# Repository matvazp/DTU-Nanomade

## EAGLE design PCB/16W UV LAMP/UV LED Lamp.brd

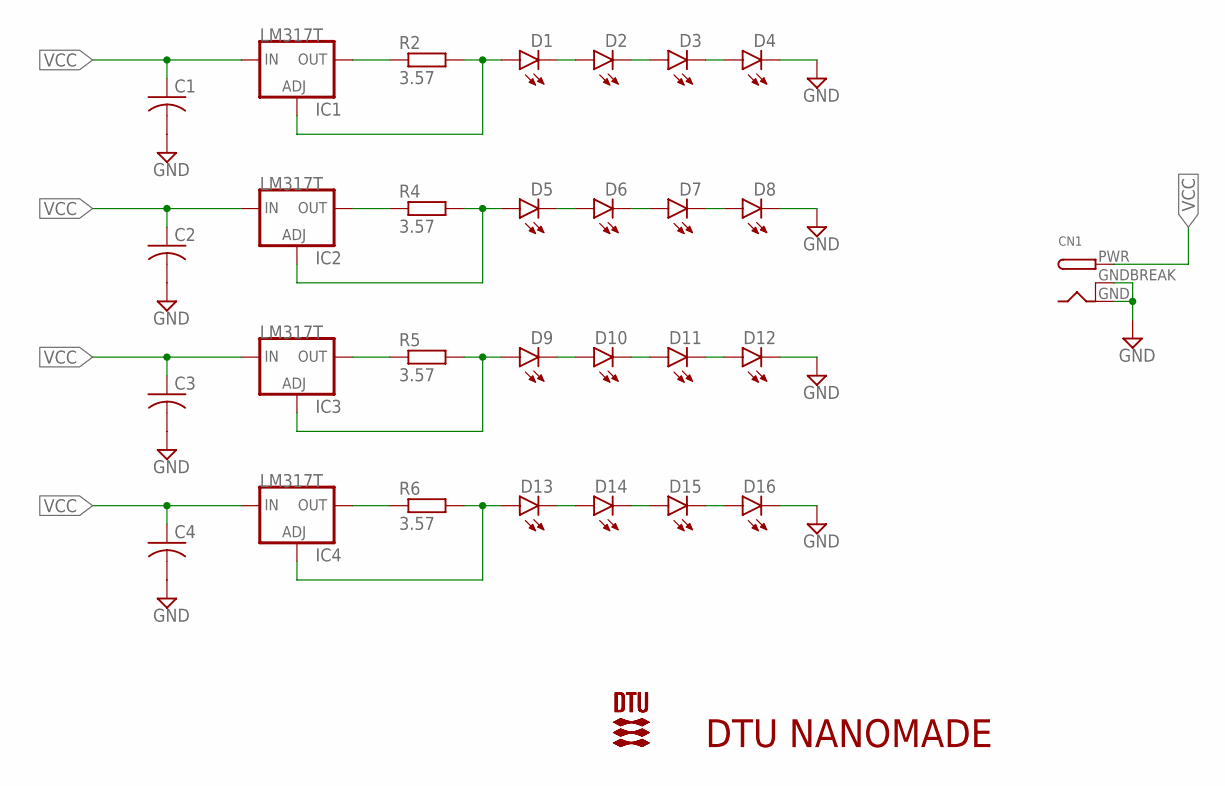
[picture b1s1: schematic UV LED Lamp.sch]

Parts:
C1, C2, C3, C4: C-USC0805K; C0805K
CN1: DCBARRELPTH; DCJACK_2MM_PTH
D1, D2, D3, D4, D5, D6, D7, D8, D9, D10, D11, D12, D13, D14, D15, D16: PM2L-1LLE-LC
IC1, IC2, IC3, IC4: LM317T; 317TL
R2, R4, R5, R6: 3.57; 0207/7
U$1, U$2: DTU_LOGO

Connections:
GND: C1.2, C2.2, C3.2, C4.2, CN1.GND, CN1.GNDBREAK, D4.P$1 (C), D8.P$1 (C), D12.P$1 (C), D16.P$1 (C)
unnamed: D1.P$1 (C), D2.P$2 (A)
unnamed: D2.P$1 (C), D3.P$2 (A)
unnamed: D3.P$1 (C), D4.P$2 (A)
unnamed: IC1.2 (OUT), R2.1
unnamed: D6.P$1 (C), D7.P$2 (A)
unnamed: D7.P$1 (C), D8.P$2 (A)
unnamed: IC2.2 (OUT), R4.1
unnamed: D9.P$1 (C), D10.P$2 (A)
unnamed: D14.P$1 (C), D15.P$2 (A)
unnamed: D13.P$1 (C), D14.P$2 (A)
unnamed: IC3.2 (OUT), R5.1
unnamed: D11.P$1 (C), D12.P$2 (A)
unnamed: D5.P$1 (C), D6.P$2 (A)
unnamed: D10.P$1 (C), D11.P$2 (A)
unnamed: D15.P$1 (C), D16.P$2 (A)
unnamed: IC4.2 (OUT), R6.1
unnamed: D1.P$2 (A), IC1.1 (ADJ), R2.2
unnamed: D5.P$2 (A), IC2.1 (ADJ), R4.2
unnamed: D9.P$2 (A), IC3.1 (ADJ), R5.2
unnamed: D13.P$2 (A), IC4.1 (ADJ), R6.2
VCC: C1.1, C2.1, C3.1, C4.1, CN1.PWR, IC1.3 (IN), IC2.3 (IN), IC3.3 (IN), IC4.3 (IN)

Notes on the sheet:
DTU NANOMADE

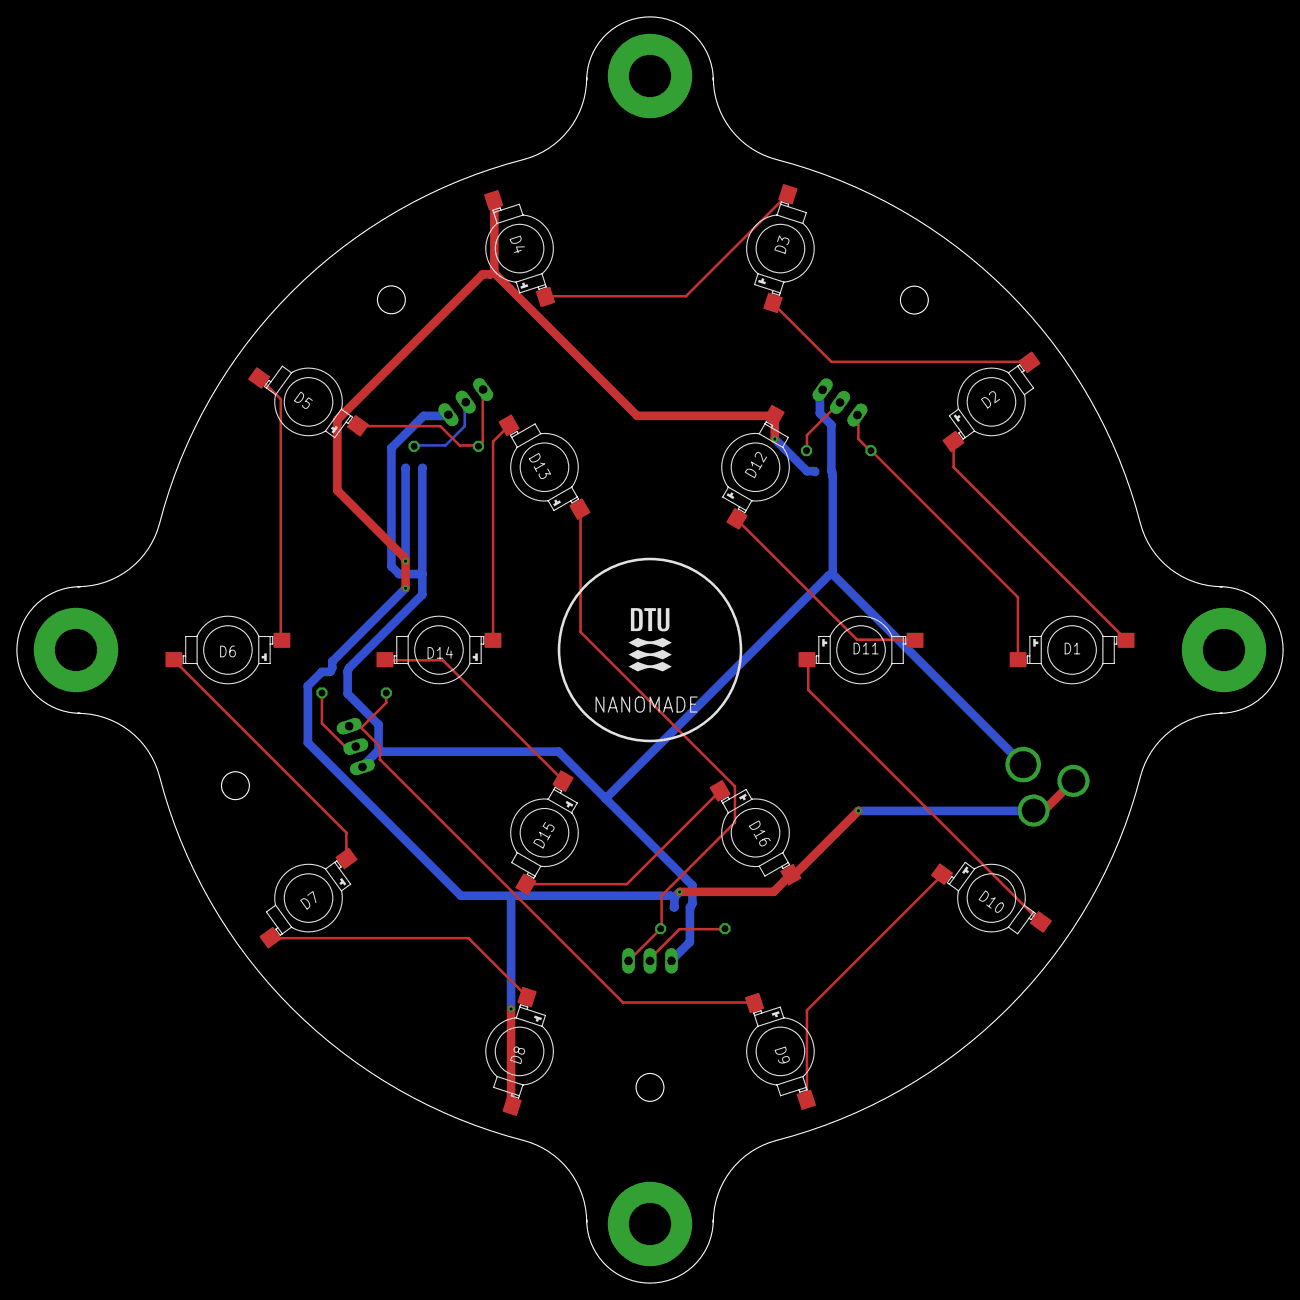
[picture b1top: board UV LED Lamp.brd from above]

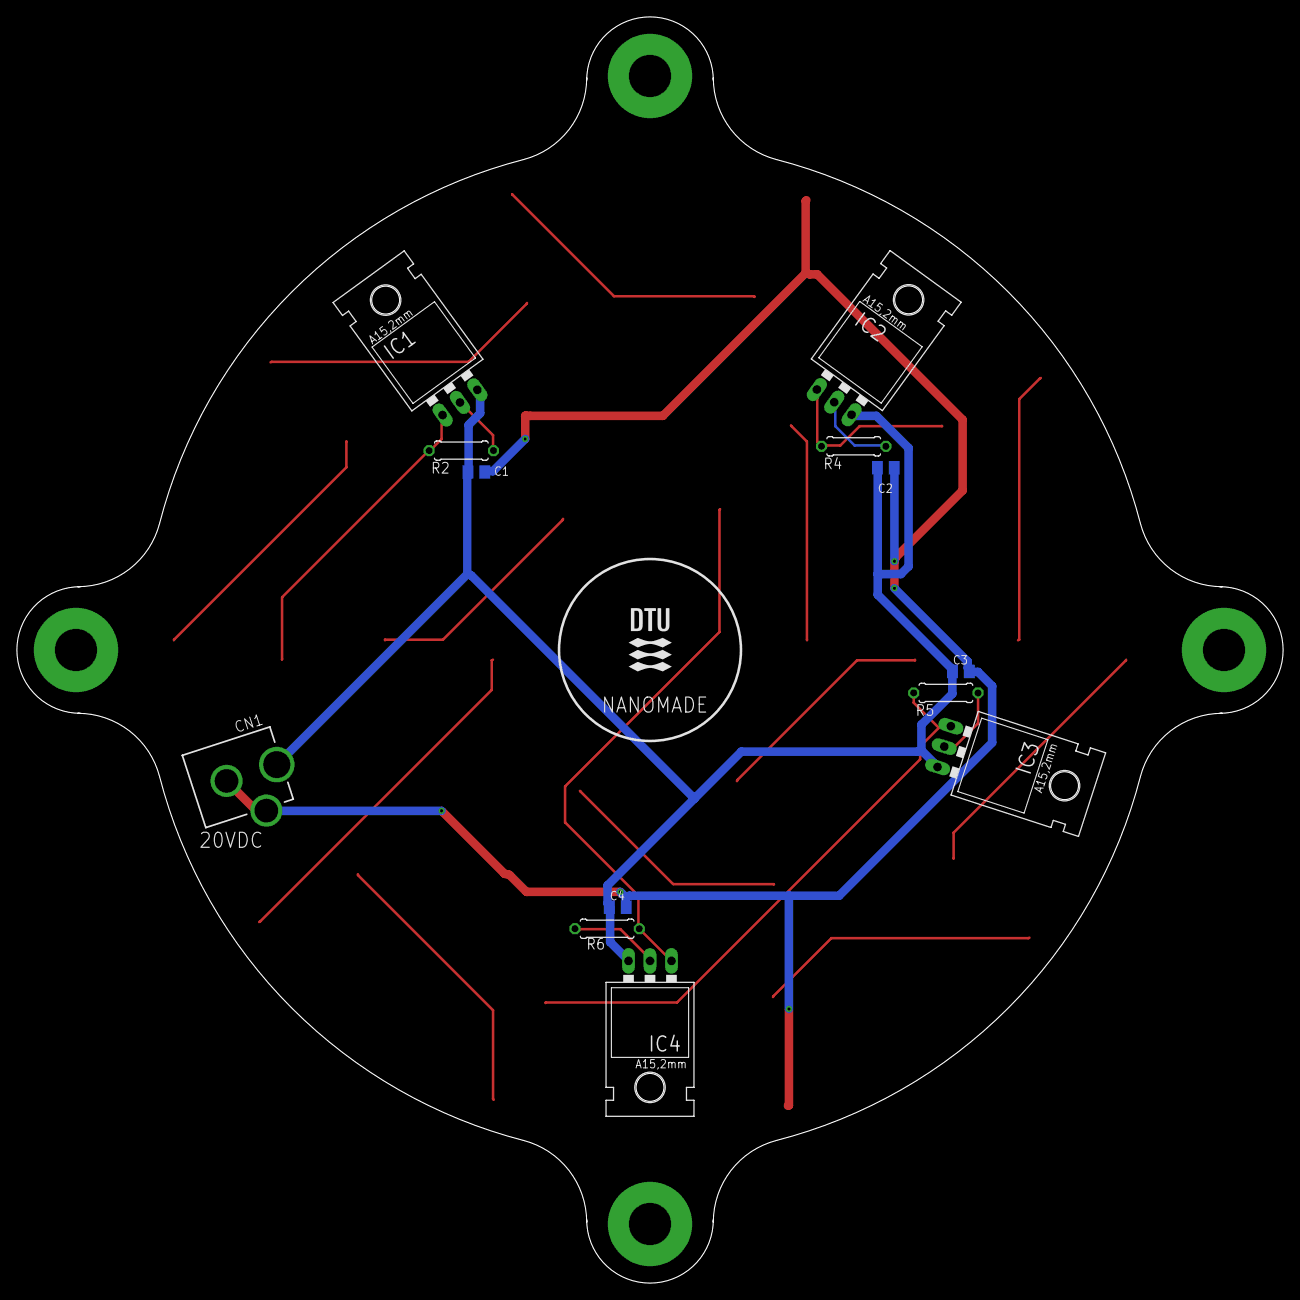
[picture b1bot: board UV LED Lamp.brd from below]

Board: 2 copper layers, 150.0 x 150.0 mm, 31 parts (14 on the bottom side), 22 nets.

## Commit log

2022-11-02 Initial commit of DTU Nanomade repository
2022-11-02 Created PCB folder
2022-11-02 Removed backup files
